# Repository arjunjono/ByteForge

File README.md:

# ByteForge

ByteForge is a handheld FPGA computer built around a custom 8-bit CPU, a small assembler, an SPI display and physical buttons. The goal is to understand how a computer works from instruction decoding through to the PCB and controls, and to run programs on the resulting device.

The current design pairs the **A1 carrier** with the **E1 enclosure**. Earlier revisions remain in the repo as a record of the design progression. The current files are gathered in [Design_Review](Design_Review/).

## E1 assembly

[Download the full STEP and editable CadQuery source](Design_Review/Assembly/ByteForge_A1_E1_STEP_Review.zip). After extraction, open `hardware/step_review/ByteForge_A1_E1_Assembly.step` for the full assembly. The archive also includes manufacturer models, CAD build scripts and enclosure STLs.

## A1 PCB and wiring

[Editable KiCad project and EasyEDA backup](Design_Review/PCB/) · [Gerbers and drill files](Design_Review/PCB/A1_Gerbers_and_Drills_REVIEW.zip) · [FPGA and assembler source](fpga/) · [Architecture documentation](ByteForge_Architecture_v13.pdf)

## Verification and build status

The A1 carrier passed KiCad ERC and PCB DRC, and the fabrication audit matched the 90 × 110 mm outline and all 94 drill hits to the PCB design. The FPGA implementation passed the saved simulation regressions and met the 27 MHz internal timing target. See [verification files](Design_Review/Verification/) and [FPGA results](fpga/docs/ENTRY13_PIN72_RESULTS.md).

This is a design review package. No boards have been ordered and physical fit and hardware operation remain untested. Check the vendor manufacturing preview and actual delivered quote before ordering.

## Bill of materials

See [BOM.csv](BOM.csv) for part numbers, supplier links and notes. Quantities cover one handheld plus a five-board lot and selected spares. Prices are planning allowances in Singapore dollars.

| Item | Needed per unit | Planned buy | Allowance (SGD) |
|---|---:|---:|---:|
| [FPGA](https://shopee.sg/Tang-Nano-20K-FPGA-Development-Board-RISCV-Linux-for-Retro-Game-Player-i.183691527.50404625405) | 1 | 1 | 70 |
| [Display](https://www.waveshare.com/product/2inch-lcd-module.htm) | 1 | 1 | 18 |
| [Carrier PCBs](https://jlcpcb.com/quote) | 1 | 5 | 25 |
| [Socket headers](https://www.digikey.sg/en/products?keywords=PPTC201LFBN-RC) | 2 | 2 | 5 |
| [LCD header](https://www.digikey.sg/en/products?keywords=PRPC008SAAN-RC) | 1 | 1 | 2 |
| [LCD regulator](https://www.digikey.sg/en/products?keywords=AP2112K-3.3TRG1) | 1 | 2 | 3 |
| [Input/output capacitors](https://www.digikey.sg/en/products?keywords=GRM21BR71C105KA01L) | 2 | 5 | 2 |
| [Decoupling capacitors](https://www.digikey.sg/en/products?keywords=GRM21BR71H104KA01L) | 2 | 5 | 2 |
| [Pull-up resistors](https://www.digikey.sg/en/products?keywords=CF14JT10K0) | 7 | 10 | 2 |
| [Tact switches](https://www.digikey.sg/en/products?keywords=B3F-1000) | 7 | 8 | 5 |
| [USB cable](https://www.digikey.sg/en/products?keywords=USB%20A%20to%20USB%20C%20data%20cable%201m) | 1 | 1 | 8 |
| [Wiring](https://www.digikey.sg/en/products?keywords=2.54mm%20jumper%20wire%20female) | 1 set | 1 set | 6 |
| [Enclosure fasteners](https://www.digikey.sg/en/products?keywords=M3%20screws%20plastic%20thread%20forming) | 1 set | 1 set | 5 |
| [Printing](https://printing.hackclub.com/) | 1 set | 1 set | 15 |
| [Shipping and taxes](https://jlcpcb.com/quote) | 1 allowance | 1 allowance | 35 |
| **Provisional total** | | | **203** |

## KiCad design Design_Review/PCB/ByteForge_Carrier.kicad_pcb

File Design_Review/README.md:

# ByteForge design review

This folder collects the current A1 + E1 files. Earlier design snapshots elsewhere in the repository are historical.

- [PCB](PCB/) — editable KiCad files with libraries, verified EasyEDA project backup, Gerbers and drills, schematic, routing, and LCD cable diagram.
- [Assembly](Assembly/) — full STEP and CadQuery source archive, plus the assembled and exploded preview. The full STEP is inside the ZIP to keep browser upload practical.
- [Verification](Verification/) — fabrication audit and saved schematic/PCB check reports.
- [Firmware and assembler](../fpga/) and [linked BOM](../BOM.csv) remain at their regular repository paths.

The parts have not been ordered. Physical fit and hardware testing remain pending.

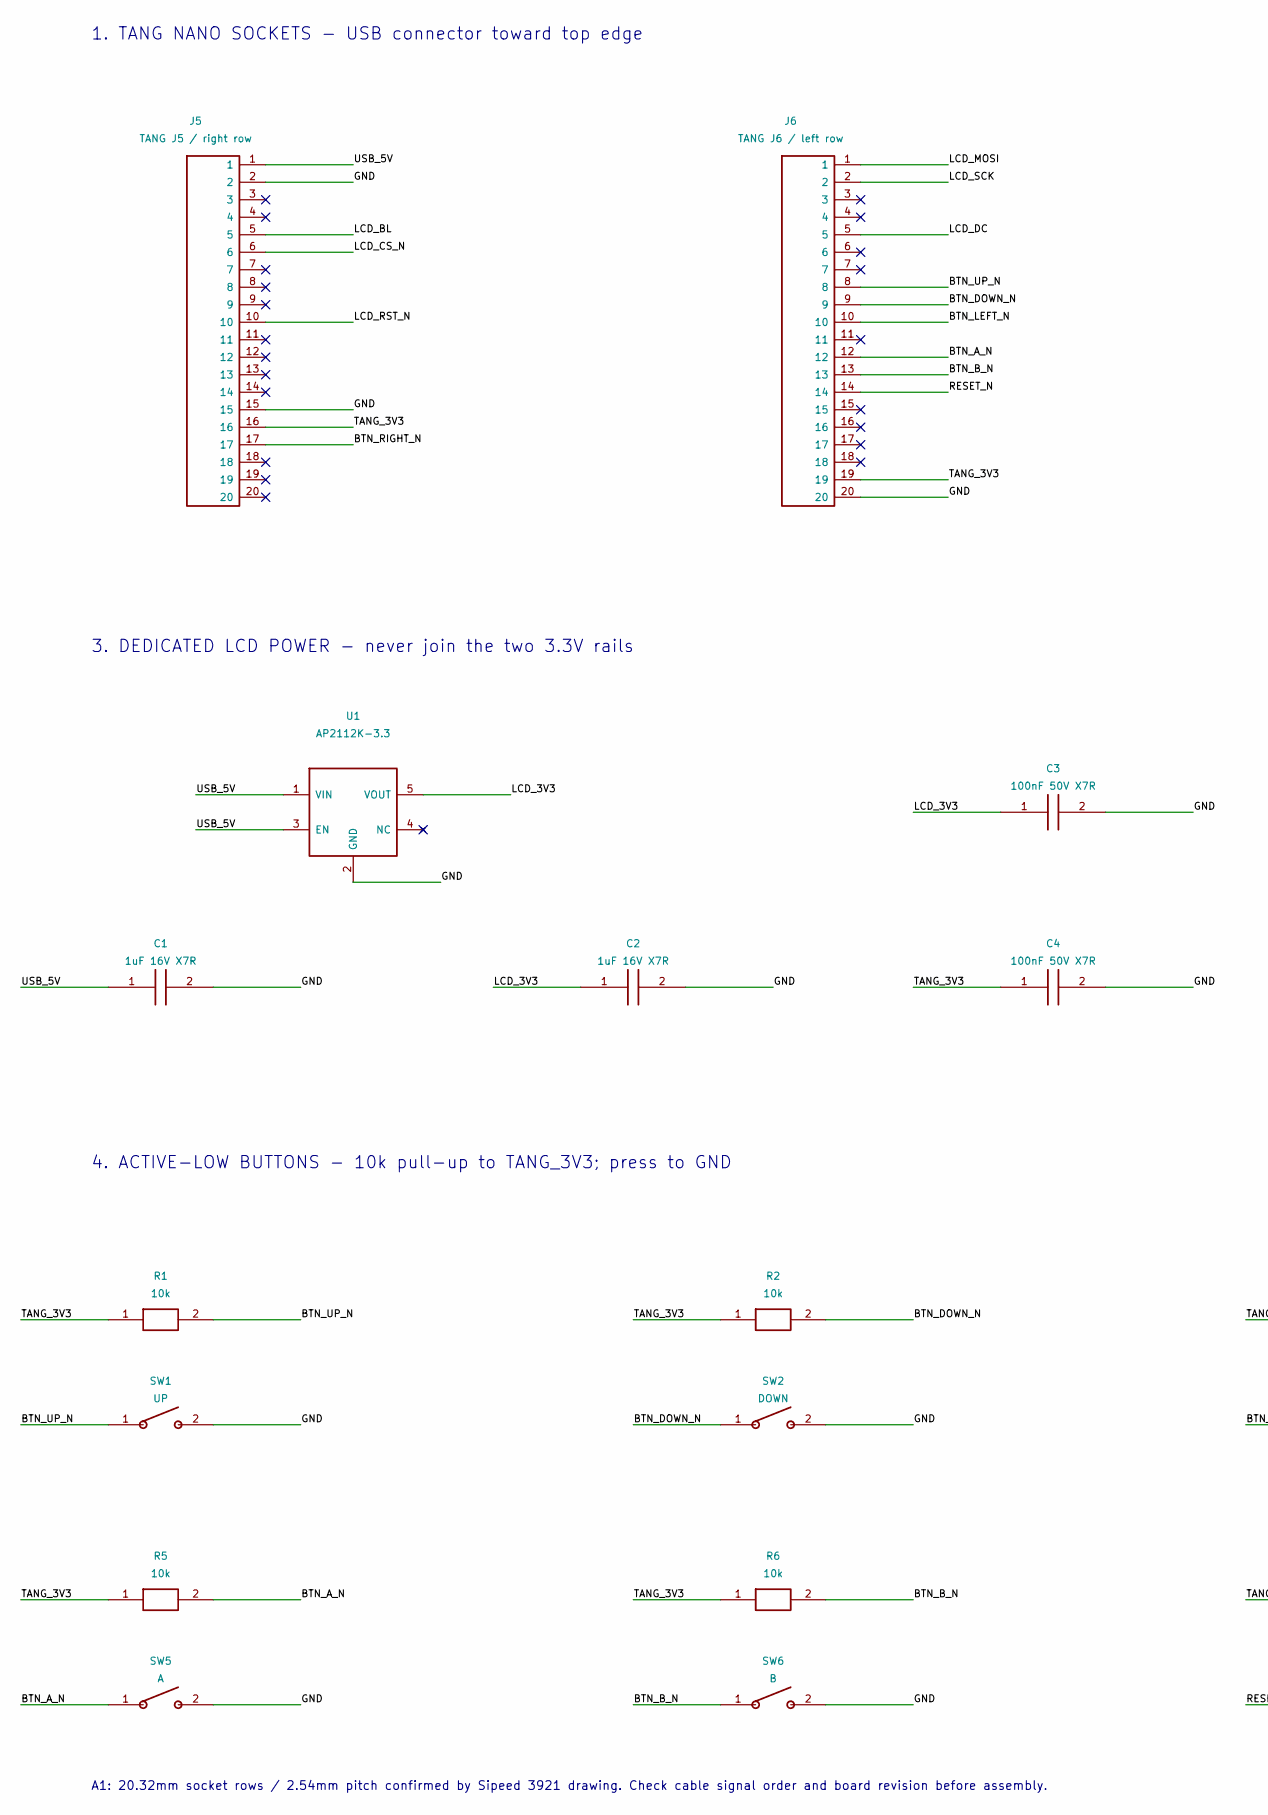
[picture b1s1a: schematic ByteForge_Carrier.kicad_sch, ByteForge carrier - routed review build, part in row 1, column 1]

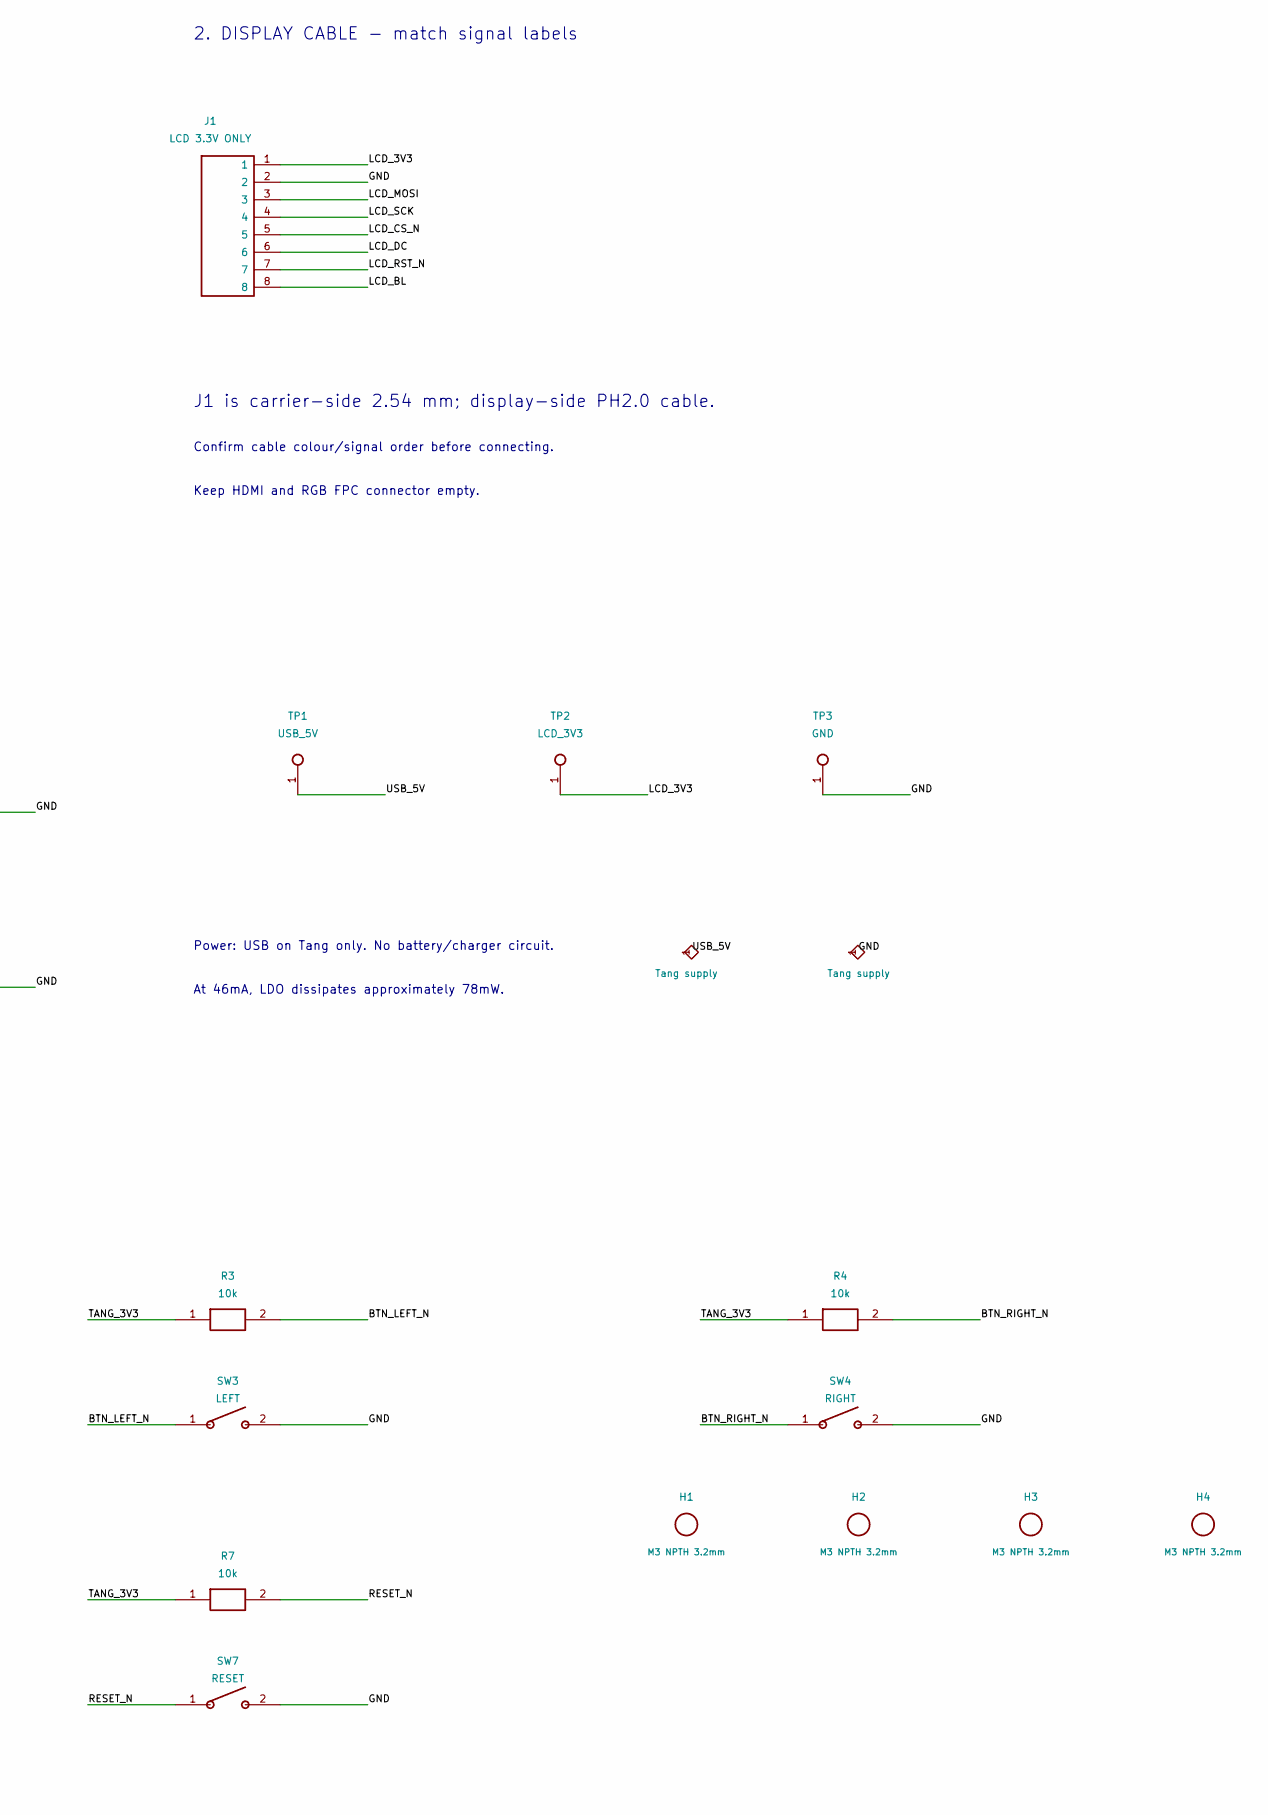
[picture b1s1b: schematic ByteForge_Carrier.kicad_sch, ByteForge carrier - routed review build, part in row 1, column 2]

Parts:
C1, C2: 1uF 16V X7R; C_0805_2012Metric
C3, C4: 100nF 50V X7R; C_0805_2012Metric
H1, H2, H3, H4: M3 NPTH 3.2mm; MountingHole_3.2mm_M3
J1: LCD 3.3V ONLY; PinHeader_1x08_P2.54mm_Vertical
J5: TANG J5 / right row; PinSocket_1x20_P2.54mm_Vertical
J6: TANG J6 / left row; PinSocket_1x20_P2.54mm_Vertical
R1, R2, R3, R4, R5, R6, R7: 10k; R_Axial_DIN0207_L6.3mm_D2.5mm_P7.62mm_Horizontal
SW1: UP; SW_PUSH_6mm
SW2: DOWN; SW_PUSH_6mm
SW3: LEFT; SW_PUSH_6mm
SW4: RIGHT; SW_PUSH_6mm
SW5: A; SW_PUSH_6mm
SW6: B; SW_PUSH_6mm
SW7: RESET; SW_PUSH_6mm
TP1: USB_5V; TestPoint_Pad_D2.0mm
TP2: LCD_3V3; TestPoint_Pad_D2.0mm
TP3: GND; TestPoint_Pad_D2.0mm
U1: AP2112K-3.3; SOT-23-5

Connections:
/BTN_A_N: J6.12, R5.2, SW5.1
/BTN_B_N: J6.13, R6.2, SW6.1
/BTN_DOWN_N: J6.9, R2.2, SW2.1
/BTN_LEFT_N: J6.10, R3.2, SW3.1
/BTN_RIGHT_N: J5.17, R4.2, SW4.1
/BTN_UP_N: J6.8, R1.2, SW1.1
/GND: C1.2, C2.2, C3.2, C4.2, J1.2, J5.2, J5.15, J6.20, SW1.2, SW2.2, SW3.2, SW4.2, SW5.2, SW6.2, SW7.2, TP3.1, U1.2 (GND)
/LCD_3V3: C2.1, C3.1, J1.1, TP2.1, U1.5 (VOUT)
/LCD_BL: J1.8, J5.5
/LCD_CS_N: J1.5, J5.6
/LCD_DC: J1.6, J6.5
/LCD_MOSI: J1.3, J6.1
/LCD_RST_N: J1.7, J5.10
/LCD_SCK: J1.4, J6.2
/RESET_N: J6.14, R7.2, SW7.1
/TANG_3V3: C4.1, J5.16, J6.19, R1.1, R2.1, R3.1, R4.1, R5.1, R6.1, R7.1
/USB_5V: C1.1, J5.1, TP1.1, U1.1 (VIN), U1.3 (EN)

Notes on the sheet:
1. TANG NANO SOCKETS - USB connector toward top edge
2. DISPLAY CABLE - match signal labels
J1 is carrier-side 2.54 mm; display-side PH2.0 cable.
Confirm cable colour/signal order before connecting.
Keep HDMI and RGB FPC connector empty.
3. DEDICATED LCD POWER - never join the two 3.3V rails
Power: USB on Tang only. No battery/charger circuit.
At 46mA, LDO dissipates approximately 78mW.
4. ACTIVE-LOW BUTTONS - 10k pull-up to TANG_3V3; press to GND
A1: 20.32mm socket rows / 2.54mm pitch confirmed by Sipeed 3921 drawing. Check cable signal order and board revision before assembly.

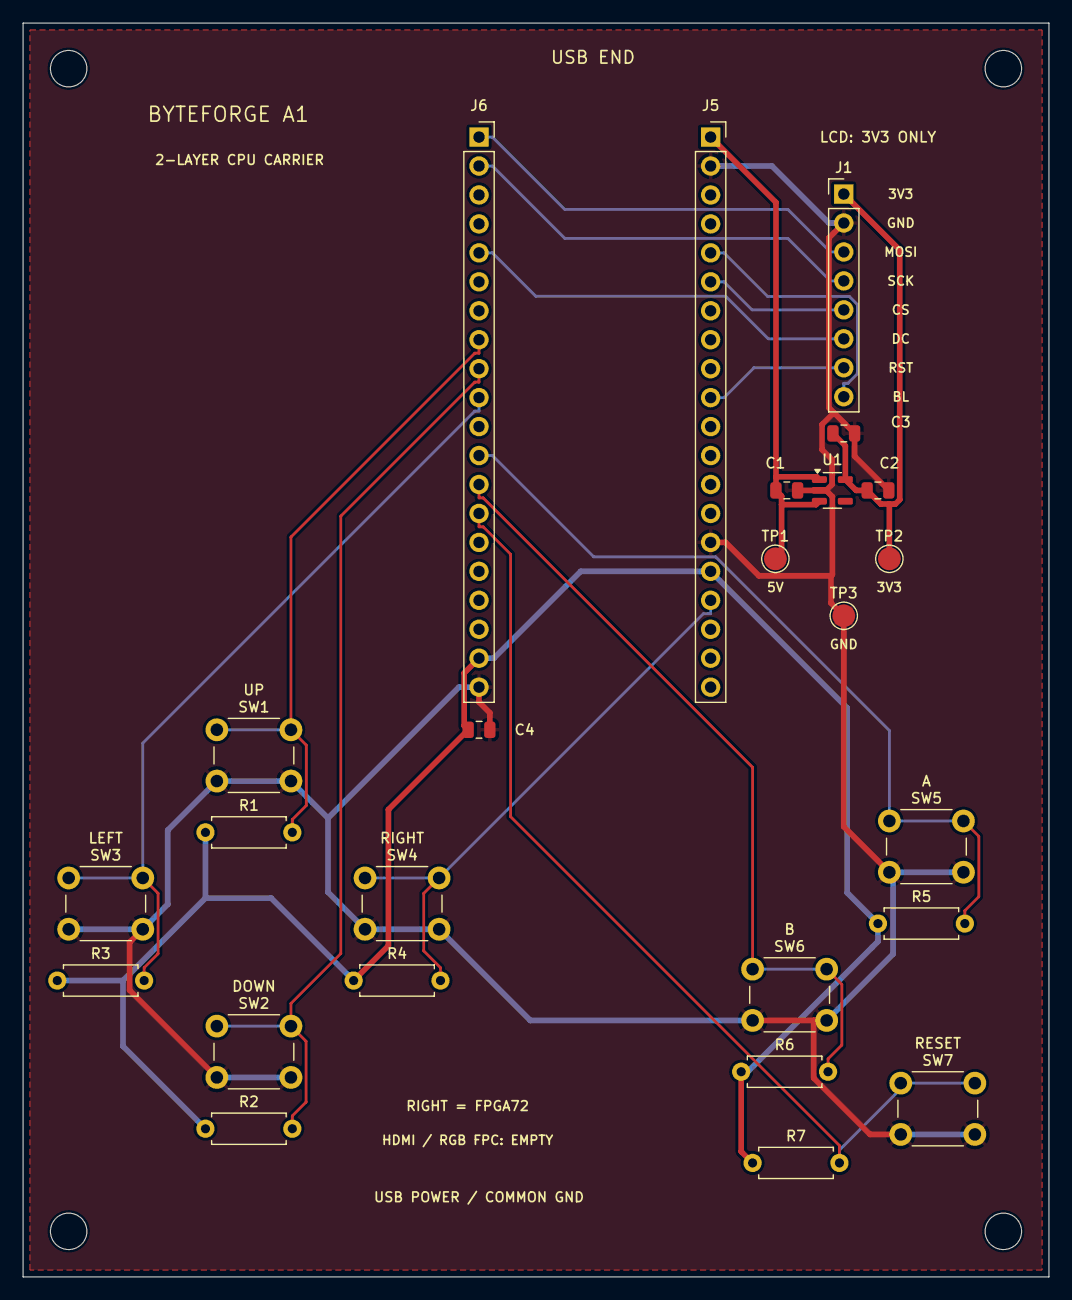
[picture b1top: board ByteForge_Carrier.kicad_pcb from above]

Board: 2 copper layers, 90.0 x 110.0 mm, 29 parts (0 on the bottom side), 17 nets.

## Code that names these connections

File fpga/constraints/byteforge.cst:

// byteforge.cst - Tang Nano 20K (GW2AR-LV18QN88C8/I7, QN88 package) physical constraints
//
// All numbers below are FPGA PACKAGE PIN numbers (the numbers on Sipeed's pin-label
// image / in the schematic net list), NOT positions on the 2x24 header strips.
// All used pins are in banks 0, 1, 4, 5 or 6; Sipeed's pinout image marks banks 0,1,5,6 as
// VIO = 3.3 V. Bank 4 (pin 42) is NOT in that legend; the schematic text extraction shows +3V3 next to
// VCCO_4 but this was NOT confirmed visually/electrically (see docs/SECTION22_23_CORRECTIONS.md B).
// LVCMOS33 is used throughout.  Net names below are from the Sipeed schematic (3921, Rev 1.30 copy).

// ---- 27 MHz crystal (Sipeed examples: IO_LOC "clk" 4, LVCMOS33) ----
IO_LOC "clk" 4;
IO_PORT "clk" IO_TYPE=LVCMOS33 PULL_MODE=UP;

// ---- Waveshare 2inch LCD (17344) on the Section 22 header pins ----
// Revision 2 remap (hardware plan): lcd_cs 75 -> 41, lcd_rst 86 -> 48. Pins 41 (PIN41_LCD_R4, IOB43A, bank 4) and
// 48 (PIN48_LCD_DE, IOR49B, bank 3) are RGB-LCD-connector nets: that connector (and HDMI) must stay disconnected.
// WARNING: lcd_din (73) and lcd_clk (74) still sit on nets labelled PIN73_HSPI_DIN2 / PIN74_HSPI_DIN3 (BL616 'HSPI')
// plus SYS_LED nets; whether the BL616 ever drives them is NOT verified.
IO_LOC "lcd_din" 73;      // IOT40A  bank 1 (nets PIN73_HSPI_DIN2 / PIN73_SYS_LED3)
IO_PORT "lcd_din" IO_TYPE=LVCMOS33 DRIVE=8 PULL_MODE=NONE;
IO_LOC "lcd_clk" 74;      // IOT34B  bank 1 (nets PIN74_HSPI_DIN3 / PIN74_SYS_LED2)
IO_PORT "lcd_clk" IO_TYPE=LVCMOS33 DRIVE=8 PULL_MODE=NONE;
IO_LOC "lcd_cs"  41;      // IOB43A  bank 4 (schematic net PIN41_LCD_R4; was pin 75; RGB connector must stay empty)
IO_PORT "lcd_cs"  IO_TYPE=LVCMOS33 DRIVE=8 PULL_MODE=UP;
IO_LOC "lcd_dc"  77;      // IOT30A  bank 1 (schematic net PIN77_LCD_CK, RGB-connector clock; connector must stay empty)
IO_PORT "lcd_dc"  IO_TYPE=LVCMOS33 DRIVE=8 PULL_MODE=NONE;
IO_LOC "lcd_rst" 48;      // IOR49B  bank 3 (schematic net PIN48_LCD_DE; was pin 86; RGB connector must stay empty)
IO_PORT "lcd_rst" IO_TYPE=LVCMOS33 DRIVE=8 PULL_MODE=NONE;
IO_LOC "lcd_bl"  42;      // IOB42B  bank 4 (schematic net PIN42_LCD_R3; connector must stay empty)
IO_PORT "lcd_bl"  IO_TYPE=LVCMOS33 DRIVE=8 PULL_MODE=DOWN;

// ---- buttons: switch to GND, internal pull-up, active low ----
IO_LOC "btn_up_n"    27;  // IOB8A   bank 5 (RGB-connector net LCD_B7)
IO_PORT "btn_up_n"    IO_TYPE=LVCMOS33 PULL_MODE=UP;
IO_LOC "btn_down_n"  28;  // IOB8B   bank 5 (LCD_B6)
IO_PORT "btn_down_n"  IO_TYPE=LVCMOS33 PULL_MODE=UP;
IO_LOC "btn_left_n"  25;  // IOB6A   bank 5 (LCD_HS)
IO_PORT "btn_left_n"  IO_TYPE=LVCMOS33 PULL_MODE=UP;
IO_LOC "btn_right_n" 26;  // IOB6B   bank 5 (LCD_VS)
IO_PORT "btn_right_n" IO_TYPE=LVCMOS33 PULL_MODE=UP;
IO_LOC "btn_a_n"     29;  // IOB14A  bank 5 (LCD_B5)
IO_PORT "btn_a_n"     IO_TYPE=LVCMOS33 PULL_MODE=UP;
IO_LOC "btn_b_n"     30;  // IOB14B  bank 5 per Apycula (schematic pin table text reads IOR14B - probable extraction typo, unresolved) (LCD_B4)
IO_PORT "btn_b_n"     IO_TYPE=LVCMOS33 PULL_MODE=UP;
IO_LOC "rst_btn_n"   31;  // IOB18A  bank 5 (LCD_B3)
IO_PORT "rst_btn_n"   IO_TYPE=LVCMOS33 PULL_MODE=UP;

// ---- on-board LEDs (active low), Sipeed blink_leds example: pins 15..20, LVCMOS33 ----
IO_LOC "led_n[0]" 15;     // IOL47A  bank 6
IO_PORT "led_n[0]" IO_TYPE=LVCMOS33 DRIVE=8 PULL_MODE=UP;
IO_LOC "led_n[1]" 16;     // IOL47B  bank 6
IO_PORT "led_n[1]" IO_TYPE=LVCMOS33 DRIVE=8 PULL_MODE=UP;
